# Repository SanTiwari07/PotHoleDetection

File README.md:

<div align="center">

# IPDS: Intelligent Pothole Detection System

### See it. Feel it. Map it.

**A low-cost dual-ESP32 + YOLOv8 rig that detects potholes in real time, tracks them, confirms each one with an accelerometer, and logs it with a severity score, GPS position and timestamp.**

<br>

<br><br>

**[Website](https://santiwari07.github.io/PotHoleDetection/)** ·
**[Paper](https://zenodo.org/records/20760578)** ·
**[Colab](https://colab.research.google.com/github/SanTiwari07/PotHoleDetection/blob/main/notebooks/quickstart.ipynb)** ·
**[Wokwi Simulation](https://wokwi.com/projects/453817129999607809)** ·
**[Docs](docs/)** ·
**[Contribute](CONTRIBUTING.md)**

<br>

<sub>YOLOv8m detections + SORT tracking on a sample road video. Each pothole keeps one ID and is logged once when it crosses the green reference line.</sub>

</div>

---

## Table of contents

- [Why IPDS?](#why-ipds)
- [Try it in 30 seconds](#try-it-in-30-seconds)
- [How it works](#how-it-works)
- [Results](#results)
- [Build the hardware](#build-the-hardware)
- [Repository structure](#repository-structure)
- [Contributing](#contributing)
- [Roadmap](#roadmap)
- [Citation](#citation)
- [Authors](#authors)
- [License](#license)

---

## Why IPDS?

Most pothole projects stop at "draw a box on an image". IPDS goes all the way from camera to a **geo-tagged, severity-ranked maintenance log**.

<table>
<tr>
<td width="33%" valign="top">

### Detect
YOLOv8m fine-tuned for potholes, reaching **mAP@0.5 = 81.7%**.

</td>
<td width="33%" valign="top">

### Track
SORT (Kalman filter + Hungarian matching) gives every pothole a stable ID, so each one is **counted once**, not once per frame.

</td>
<td width="33%" valign="top">

### Feel
When a tracked pothole reaches the wheel line, the hub asks a second ESP32 for an **MPU6050 accelerometer burst** and computes peak jerk.

</td>
</tr>
<tr>
<td width="33%" valign="top">

### Fuse
A pothole is logged only if the camera sees it **and** the accelerometer feels it. Severity (0–1) = 70% detection confidence + 30% measured impact.

</td>
<td width="33%" valign="top">

### Log
Every event goes to CSV with a DS3231 RTC timestamp and NEO-6M GPS fields, alongside an annotated MP4.

</td>
<td width="33%" valign="top">

### Cheap
Two ESP32 boards and common breakout modules, **under ₹2,500 per unit** (as reported in the paper). Inference runs on a laptop.

</td>
</tr>
</table>

---

## Try it in 30 seconds

No hardware? No problem. Pick whichever suits you:

| Option | What you get | Hardware needed |
|---|---|:---:|
|  | Run detection + tracking on a sample image or your own video | None |
|  | The ESP32 sensor node (MPU6050, NEO-6M GPS, DS3231) running in your browser | None |
| [`demo/app.py`](demo/) | Gradio web UI for images and videos (deployable as a Hugging Face Space) | None |
| Local install (below) | The full pipeline: offline on video, or live with ESP32 boards | Optional |

<!-- After deploying demo/ as a Hugging Face Space, add:

-->

### Local quickstart

```bash
git clone https://github.com/SanTiwari07/PotHoleDetection.git
cd PotHoleDetection
pip install -r requirements.txt

# Vision-only on any road video (weights auto-download on first run)
python python/main.py --source path/to/road_video.mp4
```

Outputs land in `outputs/videos/` (annotated MP4) and `outputs/logs/` (CSV). Press `q` to stop; add `--no-display` on servers.

---

## How it works

```mermaid
flowchart LR
    subgraph CAM["ESP32-CAM · vision node"]
        OV["OV2640 camera"]
    end

    subgraph HUB["Python processing hub"]
        direction TB
        Y["YOLOv8m detector"] --> S["SORT tracker"]
        S --> F["Geometric filters"]
        F -->|"pothole crosses line"| Q["Query sensor node"]
        Q --> G{"Impact felt?"}
        G -->|"yes"| SEV["Severity fusion"]
        G -->|"no"| X["Reject"]
        SEV --> OUT["CSV log + annotated MP4"]
    end

    subgraph SENSE["ESP32 · sensor node"]
        IMU["MPU6050 IMU"]
        GPS["NEO-6M GPS"]
        RTC["DS3231 RTC"]
    end

    OV -->|"WiFi · MJPEG"| Y
    Q -->|"GET /query?pothole_id=N"| SENSE
    SENSE -->|"JSON: accel, time, GPS"| G
```

> **Why two ESP32s?** Reading I²C sensors on the ESP32-CAM blocks `esp_camera_fb_get()` and tanks the frame rate. Moving all sensor I/O to a second, event-driven board keeps the video stream smooth, and both boards stay cheap.

| Step | Where | What happens |
|:---:|---|---|
| 1 | ESP32-CAM | Streams 320×240 MJPEG frames over WiFi |
| 2 | Hub | YOLOv8m detects → SORT assigns persistent IDs |
| 3 | Hub | Holds back tracks that are too large (> 25% of frame), too wide (aspect ratio > 3) or stationary for more than 10 frames |
| 4 | Hub | When a track's centre crosses the reference line, sends `GET /query?pothole_id=N` |
| 5 | Sensor node | Returns accelerometer, RTC timestamp and GPS fields as JSON |
| 6 | Hub | Computes peak jerk. No impact means the event is rejected; otherwise it computes severity, appends a CSV row and annotates the video |

### Severity scoring

```
jerk_norm = min(peak_jerk / 20 m/s³, 1)
severity  = 0.7 × YOLO confidence + 0.3 × jerk_norm
```

These are Eqs. 6–7 of the paper, implemented in [`python/pothole_detection/fusion.py`](python/pothole_detection/fusion.py). Events whose peak jerk is below `--jerk-threshold` (default 1.5 m/s³; calibrate it for your vehicle) are rejected by the fusion gate. In offline mode there is no sensor node, so the gate is skipped, severity is vision-only, and the jerk/GPS columns are left empty.

**Deep dives:** [Architecture](docs/ARCHITECTURE.md) · [Hardware & wiring](docs/HARDWARE.md) · [Full technical spec](docs/DETAIL.md) · [Paper (PDF)](docs/IPDS_Pothole_Detection.pdf) · [Project website](https://santiwari07.github.io/PotHoleDetection/)

---

## Results

### Model (validation split)

| mAP@0.5 | mAP@0.5:0.95 | Precision | Recall |
|:---:|:---:|:---:|:---:|
| **81.68%** | **55.95%** | **82.33%** | **74.42%** |

YOLOv8m, 640×640 input, single class (`pothole`), trained on the [Pothole Detection dataset by andrewmvd on Kaggle](https://www.kaggle.com/datasets/andrewmvd/pothole-detection) (665 images with bounding boxes; Pascal VOC XML converted to YOLO format; 598 training / 67 validation images). Weights: [Releases → v1.0](https://github.com/SanTiwari07/PotHoleDetection/releases/tag/v1.0).

```python
from ultralytics import YOLO
model = YOLO("assets/models/pothole_yolov8.pt")
model.predict("road.jpg", conf=0.25)[0].show()
```

### System performance (reported in the paper)

| Measure | Result |
|---|---|
| Inference speed | 10–15 FPS on a CPU-only laptop (320×240 input) |
| Latency, frame capture → CSV row | ~170–200 ms |
| Hardware cost | under ₹2,500 per unit |

The paper also reports false-positive trials (shadows, manhole covers, speed bumps and others); see [docs/DETAIL.md](docs/DETAIL.md#7-reported-system-results-paper).

### Sample field log (20 March 2026)

[`outputs/sample_logs/output.csv`](outputs/sample_logs/output.csv) has 50 logged potholes from a drive between 1:56 and 2:08 pm. It uses the same columns as the log `main.py` writes. The original, older-format file (text severity bands, `pothole_001` IDs, `01:56 pm` times) is kept as [`output_legacy.csv`](outputs/sample_logs/output_legacy.csv), and [`python/convert_legacy_log.py`](python/convert_legacy_log.py) converts any log in that format:

```bash
python python/convert_legacy_log.py outputs/sample_logs/output_legacy.csv -o outputs/sample_logs/output.csv
```

The script turns `01:56 pm` into `13:56:00` (the old log has no seconds, so they are `00`), `pothole_001` into `1`, and each Low / Medium / High band into the 0–1 score computed from that row's own `confidence` and `peak_jerk`. Rows already in the current format are left unchanged. The bands in the legacy file were assigned by peak jerk:

| Band | Peak jerk in the file | Rows | Share |
|---|---|:---:|:---:|
| Low | 1.6 – 2.7 | 8 | 16% |
| Medium | 3.0 – 5.9 | 22 | 44% |
| High | 6.0 – 9.4 | 20 | 40% |

<details>
<summary><b>CSV column reference</b></summary>

| Column | Description |
|---|---|
| `date`, `time` | Detection timestamp (DS3231 RTC; falls back to host clock) |
| `frame_id` | Video frame number when the event was triggered |
| `pothole_id` | Unique SORT track ID |
| `confidence` | YOLOv8 detection confidence (0–1) |
| `bounding_box_area` | Box area in px² |
| `aspect_ratio` | Box width / height |
| `peak_jerk` | Peak jerk from the MPU6050 burst (m/s³; empty in offline mode) |
| `severity` | Severity score 0–1 |
| `latitude`, `longitude` | WGS-84 position from the NEO-6M (`0` without a GPS fix; empty in offline mode) |

</details>

<details>
<summary><b>Reproduce the model</b></summary>

```bash
# 1. Download and unzip https://www.kaggle.com/datasets/andrewmvd/pothole-detection
python training/prepare_dataset.py --src path/to/pothole-detection   # VOC XML -> YOLO, 598 train / 67 val
python training/train.py                                              # YOLOv8m, 640px, 100 epochs, AdamW
```

The best checkpoint is copied to `assets/models/pothole_yolov8.pt` and validation metrics are printed at the end. The split sizes match the paper, but the paper doesn't publish which images were in each split, so your metrics may differ slightly.

</details>

---

## Build the hardware

### The prototype

Two hand-wired perfboard decks: the ESP32-CAM vision node on top, and the ESP32 sensor node with the MPU6050, DS3231 and NEO-6M below. The [custom PCB](#custom-pcb) replaces the lower deck.

<table>
<tr>
<td width="33%" align="center"><br><sub><b>Assembled rig</b>: camera deck above, sensor deck below</sub></td>
<td width="33%" align="center"><br><sub><b>Vision node</b>: ESP32-CAM with the OV2640 camera</sub></td>
<td width="33%" align="center"><br><sub><b>Hand-wired underside</b>: point-to-point wiring of the sensor deck</sub></td>
</tr>
</table>

### Components

| Component | Role |
|---|---|
| **ESP32-CAM** (AI-Thinker, OV2640) | Vision node: continuous MJPEG stream |
| **ESP32 dev board** | Sensor node: answers HTTP queries on demand |
| **MPU6050** | 6-axis IMU: peak jerk while crossing the pothole |
| **NEO-6M GPS** | Latitude / longitude |
| **DS3231 RTC** | Accurate timestamps without internet |
| **Laptop or edge device** | Runs YOLOv8 inference (e.g. Jetson Nano) |

### Sensor-node wiring

| Module pin | ESP32 pin |
|---|---|
| MPU6050 SDA / DS3231 SDA | GPIO21 (+ 4.7 kΩ pull-up to 3V3) |
| MPU6050 SCL / DS3231 SCL | GPIO22 (+ 4.7 kΩ pull-up to 3V3) |
| MPU6050 **AD0** | **3V3** (sets address 0x69; the DS3231 already uses 0x68) |
| NEO-6M TX → | GPIO16 (RX2) |
| NEO-6M RX ← | GPIO17 (TX2) |
| All VCC / GND | 3V3 / GND |

### Custom PCB

A 2-layer carrier board for the ESP32-DevKitC and the three modules is in [`KiCad/IPDS_SensorNode/`](KiCad/IPDS_SensorNode/). It passes KiCad's ERC/DRC with 0 violations, and ready-to-order Gerbers, a BOM and a schematic PDF are in its `fabrication/` folder. Interactive diagrams: [`Diagrams/`](Diagrams/).

### Setup

1. **WiFi credentials.** Both boards and the laptop join the same network (a phone hotspot works):
   ```bash
   cp .env.example .env        # then edit WIFI_SSID / WIFI_PASSWORD
   python update_wifi.py       # generates credentials.h for both sketches (git-ignored)
   ```
2. **Flash the firmware** with Arduino IDE 2.x + ESP32 core 3.x (sensor node also needs the `RTClib` and `TinyGPSPlus` libraries):

   | Sketch | Board |
   |---|---|
   | [`ESP_32_Code/esp_32_cam_final/`](ESP_32_Code/esp_32_cam_final/) | AI-Thinker ESP32-CAM |
   | [`ESP_32_Code/esp_32_final/`](ESP_32_Code/esp_32_final/) | ESP32 Dev Module |

3. **Set the device IPs** printed on each Serial Monitor (115200 baud) in `.env` (`ESP32_CAM_IP`, `ESP32_SENSOR_IP`). Open `http://<sensor-ip>/` in a browser to check that the MPU6050, RTC and GPS are all detected (the GPS needs a clear sky view for its first fix).
4. **Calibrate the MPU6050** once, mounted in the vehicle: flash [`ESP_32_Code/mpu6050_calibration`](ESP_32_Code/mpu6050_calibration/), paste the printed offsets into `esp_32_final.ino` and re-flash it ([details](docs/HARDWARE.md#mpu6050-calibration)).
5. **Run live:**
   ```bash
   python python/main.py --live
   ```

<details>
<summary><b>All CLI options</b></summary>

| Flag | Default | Description |
|---|---|---|
| `--source` | first `.mp4` in `assets/videos/` | Offline mode: video path or webcam index |
| `--live` | off | Stream from the ESP32-CAM and query the sensor node |
| `--cam-ip`, `--sensor-ip` | from `.env` | Override device IPs |
| `--model` | `assets/models/pothole_yolov8.pt` | Weights (auto-downloaded if missing) |
| `--conf` | `0.25` | Detection confidence threshold |
| `--jerk-threshold` | `1.5` | Live mode: minimum peak jerk (m/s³) that confirms an impact |
| `--output-dir` | `outputs/` | Where the MP4 and CSV are written |
| `--no-display` | off | Headless mode |

</details>

### See your potholes on a map

Convert any log to GeoJSON and open it in [geojson.io](https://geojson.io), QGIS, uMap or Google My Maps:

```bash
python python/export_geojson.py outputs/sample_logs/output.csv -o potholes.geojson
```

Rows without a GPS position (offline runs, or no GPS fix) are skipped and counted.

---

## Repository structure

```text
PotHoleDetection/
├── python/
│   ├── main.py                    # Entry point: detection → tracking → fusion → logging
│   ├── export_geojson.py          # CSV log → GeoJSON for QGIS / geojson.io
│   └── pothole_detection/
│       ├── detector.py            # YOLOv8 wrapper
│       ├── tracker.py             # SORT wrapper with unique-ID counting
│       ├── sort.py                # SORT (Bewley et al., GPL-3.0)
│       ├── filters.py             # Area / aspect-ratio / persistence filters
│       ├── fusion.py              # Jerk, fusion gate, severity score
│       └── geojson_export.py      # Log rows → GeoJSON features
├── ESP_32_Code/
│   ├── esp_32_cam_final/          # Vision node firmware (MJPEG server)
│   ├── esp_32_final/              # Sensor node firmware (HTTP /query API)
│   └── mpu6050_calibration/       # One-time MPU6050 offset calibration
├── PotHoleSimu/                   # Wokwi simulation of the sensor node
├── demo/                          # Gradio app / Hugging Face Space
├── notebooks/quickstart.ipynb     # Colab quickstart
├── training/                      # Dataset conversion + YOLOv8 training scripts
├── KiCad/                         # Sensor-node schematic and PCB
├── Diagrams/                      # Interactive HTML block diagrams
├── assets/                        # Demo GIF and hardware photos
├── index.html                     # Project website (GitHub Pages)
├── docs/                          # Architecture, hardware, full spec, paper PDF
├── outputs/sample_logs/           # Field-test CSV
├── tests/                         # Unit tests (pytest)
├── update_wifi.py                 # .env → credentials.h generator
└── .env.example                   # Config template (copy to .env)
```

---

## Contributing
PotHoleDetection is an open-source project that welcomes contributions from everyone. Whether you're fixing a bug, improving documentation, enhancing pothole detection accuracy, or adding new features, every contribution makes a difference. Real-world road images and pothole data from your city are especially valuable for improving the system.

**Good places to start**

- **Found a bug or have an idea?** [Open an issue](https://github.com/SanTiwari07/PotHoleDetection/issues/new/choose).
- **First contribution?** Look for [`good first issue`](https://github.com/SanTiwari07/PotHoleDetection/labels/good%20first%20issue) and [`help wanted`](https://github.com/SanTiwari07/PotHoleDetection/labels/help%20wanted).
- **Want something bigger?** Pick an item from the [roadmap](#roadmap) below.

**Dev setup in four commands**

```bash
git clone https://github.com/SanTiwari07/PotHoleDetection.git
cd PotHoleDetection
pip install -r requirements-dev.txt
pytest tests
```

Then fork, branch from `main`, keep each PR focused, and make sure `pytest tests` passes. **Never commit credentials** (`.env` and `credentials.h` are git-ignored). The full guide is in [**CONTRIBUTING.md**](CONTRIBUTING.md).

**Built one, or tried it on your roads?** Tell us, whatever the result. Post photos, logs or false-positive clips in [Discussions](https://github.com/SanTiwari07/PotHoleDetection/discussions) or in the [field data issue](https://github.com/SanTiwari07/PotHoleDetection/issues/10). Real-world data from other cities is the most useful contribution you can make.

### Contributors

---

## Roadmap

- [ ] Smartphone / dashcam mode (no ESP32 needed)
- [x] Export detections to GeoJSON ([`export_geojson.py`](python/export_geojson.py))
- [ ] Edge deployment on Coral TPU / Hailo-8 / Jetson
- [ ] Docker image for the processing hub
- [ ] Web dashboard with a live pothole heatmap
- [ ] Segmentation model for pothole area / depth estimation

---

## Citation

If you use IPDS in your research, please cite the paper ([Zenodo record](https://zenodo.org/records/20760578)) or the software:

```bibtex
@software{tiwari2026ipds,
  author    = {Tiwari, Sanskar and Bansod, Swarali and Kognole, Eshwari and Shinde, Shruti},
  title     = {Real-Time Pothole Detection Based on Vision-Dominant Sensor Fusion
               and Dual ESP32 Architecture},
  year      = {2026},
  version   = {1.0.0},
  license   = {MIT},
  url       = {https://github.com/SanTiwari07/PotHoleDetection}
}
```

A machine-readable [`CITATION.cff`](CITATION.cff) is included; GitHub's **"Cite this repository"** button uses it.

---

## Authors

| Name | Role |
|---|---|
| **Sanskar Tiwari** | Core architecture & ML pipeline |
| **Swarali Bansod** | Sensor integration & firmware |
| **Eshwari Kognole** | Hardware design & testing |
| **Shruti Shinde** | Data collection & validation |

## License

Project code is released under the [MIT License](LICENSE).

Third-party components keep their own licenses: [`sort.py`](python/pothole_detection/sort.py) is © Alex Bewley under **GPL-3.0**, and [Ultralytics YOLOv8](https://github.com/ultralytics/ultralytics) is **AGPL-3.0**.

---

<div align="center">

### If IPDS is useful to you, please give it a star on GitHub. It helps others find the project!

</div>

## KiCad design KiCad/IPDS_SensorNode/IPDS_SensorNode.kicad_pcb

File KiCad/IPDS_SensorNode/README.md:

# IPDS Sensor Node: KiCad PCB

Carrier board for the IPDS sensor node: an **ESP32-DevKitC (38-pin)** plus plug-in **MPU6050**, **DS3231 RTC** and **NEO-6M GPS** breakout modules. Every module sits in a female header, so nothing is soldered to the modules themselves.

**Board:** 117 × 68 mm · 2 layers · 1.6 mm FR4 · GND pour on both sides · 4 × M3 mounting holes
**Made with:** KiCad 10.0 (open with KiCad 10 or newer)

### Verification status

Checked with `kicad-cli` (KiCad 10.0.6):

| Check | Result |
|---|---|
| ERC (schematic) | **0 violations** |
| DRC (PCB, all severities) | **0 violations**, **0 unconnected items** |
| Schematic ↔ PCB parity | **0 issues** |

```bash
kicad-cli sch erc --severity-all IPDS_SensorNode.kicad_sch
kicad-cli pcb drc --severity-all --schematic-parity IPDS_SensorNode.kicad_pcb
```

---

## Files

| File | Description |
|---|---|
| `IPDS_SensorNode.kicad_pro` | Project settings and design rules |
| `IPDS_SensorNode.kicad_sch` | Schematic |
| `IPDS_SensorNode.kicad_pcb` | PCB layout |
| `IPDS.kicad_sym` | Project symbols: ESP32-DevKitC and the three breakout modules (named pins) |
| `IPDS.pretty/` | Project footprint: ESP32-DevKitC 38-pin socket |
| `fabrication/IPDS_SensorNode_gerbers.zip` | Gerbers + Excellon drill files, ready to upload to a PCB fab |
| `fabrication/IPDS_SensorNode_schematic.pdf` | Schematic as PDF |
| `fabrication/IPDS_SensorNode_BOM.csv` | Bill of materials |

---

## Connections

| Net | ESP32 pin | Connected to |
|---|---|---|
| `+3V3` | 3V3 (onboard regulator) | MPU VCC, MPU **AD0**, RTC VCC, GPS VCC, R1, R2, C1, C2 |
| `GND` | GND ×3 | All modules, J1 pin 2, C1, C2 |
| `+5V` | 5V | D1 cathode (external 5 V input) |
| `SDA` | GPIO21 | MPU SDA, RTC SDA, R1 4.7 kΩ pull-up |
| `SCL` | GPIO22 | MPU SCL, RTC SCL, R2 4.7 kΩ pull-up |
| `ESP_TX2` | GPIO17 (TX2) | GPS **RX** |
| `ESP_RX2` | GPIO16 (RX2) | GPS **TX** |
| `VIN_EXT` | n/a | J1 pin 1 → D1 anode |

### I²C addresses

| Device | Address | Note |
|---|---|---|
| DS3231 RTC | `0x68` | fixed |
| AT24C32 EEPROM (on the ZS-042 board) | `0x57` | unused |
| MPU6050 | **`0x69`** | AD0 is tied to 3V3 on this PCB, because `0x68` is already taken by the DS3231 |

The sensor firmware (`ESP_32_Code/esp_32_final`) uses exactly these pins and addresses. GPS UART runs at 9600 baud, 8N1.

### Module pin order (match the silkscreen)

| Socket | Module | Pin order (pin 1 = square pad, top) |
|---|---|---|
| U2 (1×8) | GY-521 MPU6050 | VCC, GND, SCL, SDA, XDA, XCL, AD0, INT |
| U3 (1×6) | ZS-042 DS3231 | 32K, SQW, SCL, SDA, VCC, GND |
| U4 (1×4) | GY-NEO6MV2 | VCC, RX, TX, GND |

Breakout boards from different sellers sometimes order their pins differently. **Check your module's printed labels against the table before plugging it in.**

---

## Before you order

1. **Measure your ESP32 board.** The footprint expects the two pin rows **25.4 mm (1.0") apart**, as on Espressif's DevKitC V4 and most 38-pin clones. Some "narrow" clones are 22.86 mm; if yours is, move the right-hand row in `IPDS.pretty`.
2. **Power:** feed 5 V into J1 (e.g. a car USB adapter) **or** use the DevKit's USB port. If your DevKit has no diode on its USB 5 V line, don't connect both at once: D1 stops J1 from being back-fed, but USB could be back-fed from J1.
3. **ZS-042 with a CR2032:** the module has a charging circuit meant for rechargeable LIR2032 cells. With a normal CR2032, remove its 200 Ω resistor (or the diode next to it).

## Bill of materials

| Qty | Ref | Part | Notes |
|---|---|---|---|
| 1 | U1 | ESP32-DevKitC 38-pin | plus **2 × 1×19 female headers**, 2.54 mm |
| 1 | U2 | GY-521 MPU6050 module | 1×8 female header |
| 1 | U3 | ZS-042 DS3231 module + CR2032 | 1×6 female header |
| 1 | U4 | GY-NEO6MV2 NEO-6M GPS module + antenna | 1×4 female header |
| 1 | J1 | Phoenix MKDS 1,5/2-5.08 screw terminal | or any 5.08 mm 2-pin terminal |
| 1 | D1 | SS14 Schottky diode, SMA | 1 A, 40 V |
| 2 | R1, R2 | 4.7 kΩ, 0805 | I²C pull-ups |
| 1 | C1 | 100 nF, 0805 | decoupling |
| 1 | C2 | 10 µF, 0805, ≥10 V | bulk |
| 4 | — | M3 standoffs + screws | mounting |

## Ordering the PCB

Upload `fabrication/IPDS_SensorNode_gerbers.zip` to JLCPCB, PCBWay or a similar fab with the defaults: 2 layers, 1.6 mm, HASL, 1 oz copper. All tracks are ≥ 0.25 mm and clearances ≥ 0.2 mm, so standard (cheapest) capabilities are enough.

To regenerate the outputs after editing: **File → Fabrication Outputs → Gerbers** and **Drill Files** in the PCB editor, after re-running **Inspect → Design Rules Checker**.

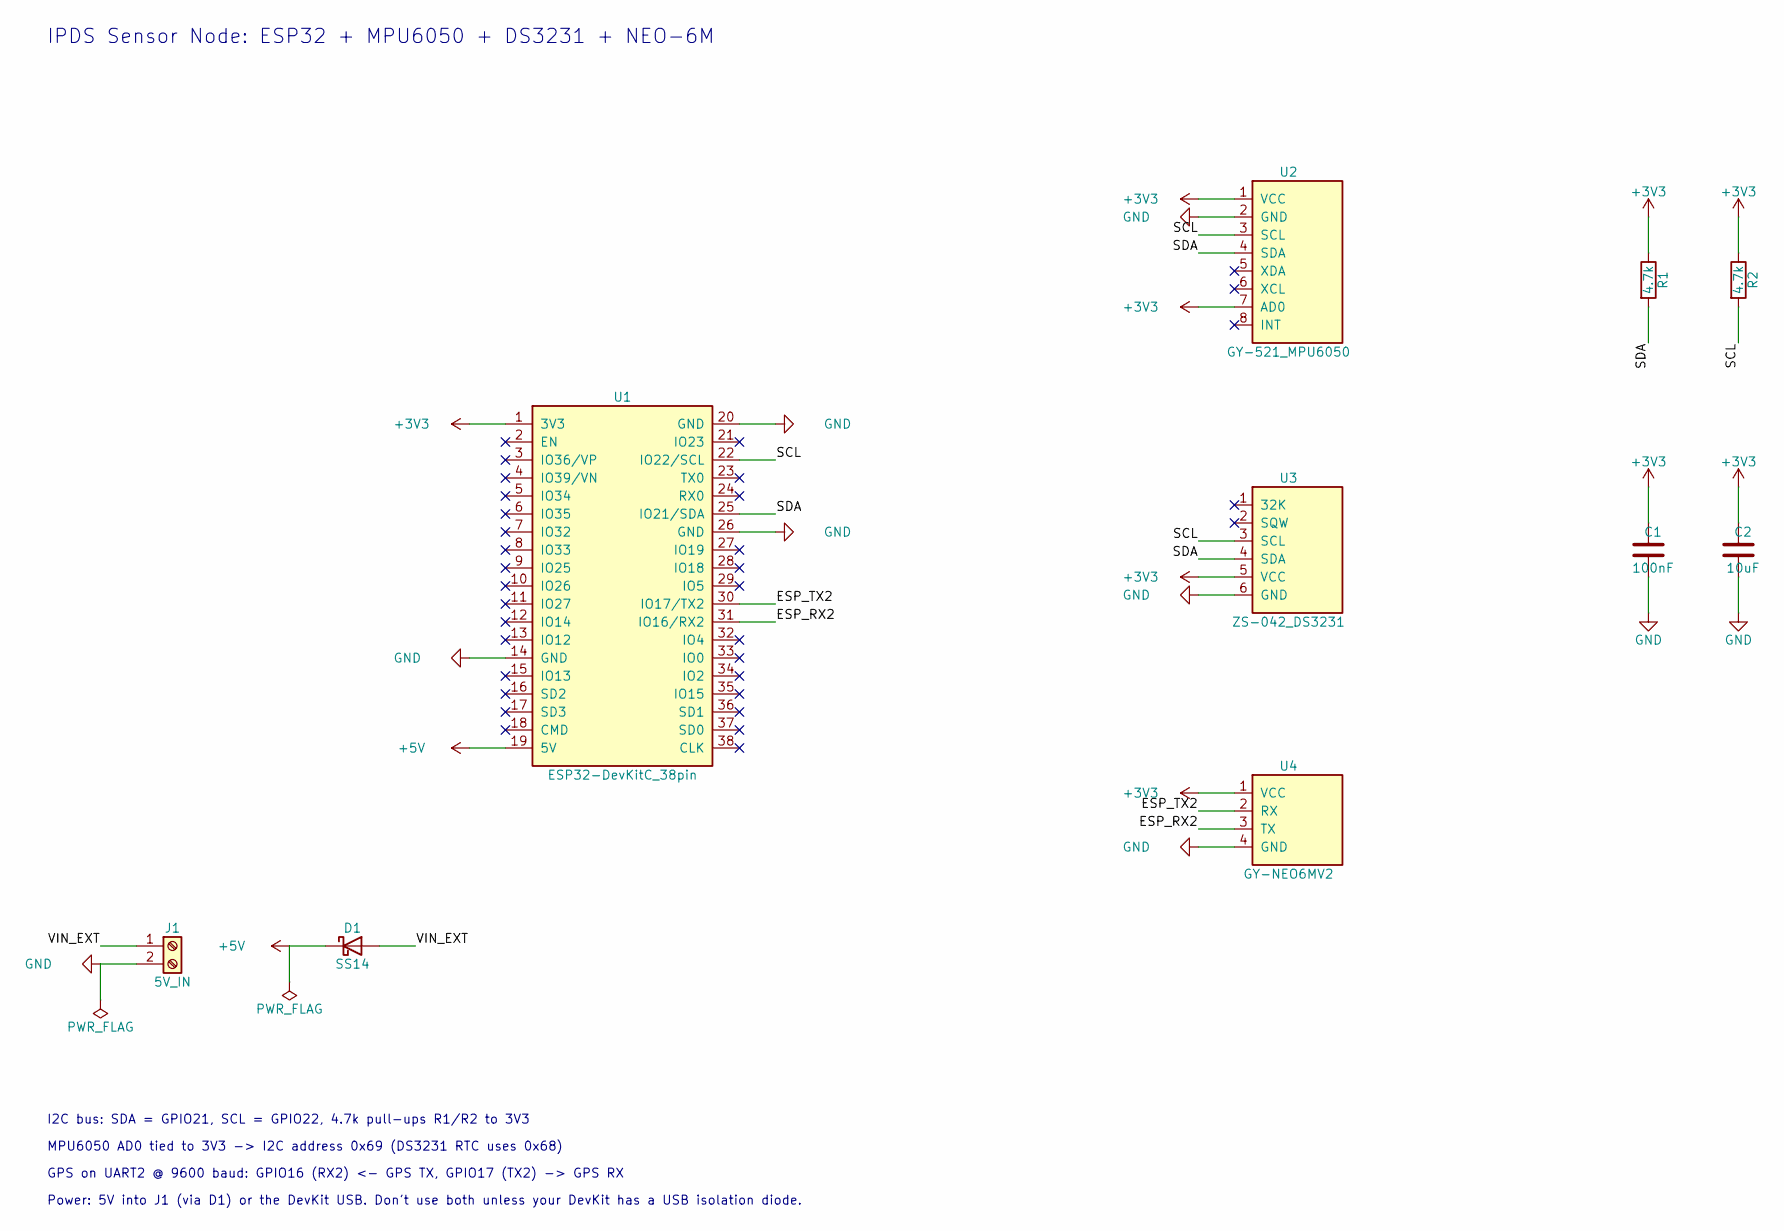
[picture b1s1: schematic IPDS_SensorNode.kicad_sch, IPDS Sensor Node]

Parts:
C1: 100nF; C_0805_2012Metric
C2: 10uF; C_0805_2012Metric
D1: SS14; D_SMA
J1: 5V_IN; TerminalBlock_Phoenix_MKDS-1,5-2-5.08_1x02_P5.08mm_Horizont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
R1, R2: 4.7k; R_0805_2012Metric
U1: ESP32-DevKitC_38pin; ESP32_DevKitC_38_Socket
U2: GY-521_MPU6050; PinSocket_1x08_P2.54mm_Vertical
U3: ZS-042_DS3231; PinSocket_1x06_P2.54mm_Vertical
U4: GY-NEO6MV2; PinSocket_1x04_P2.54mm_Vertical

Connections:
+3V3: C1.1, C2.1, R1.1, R2.1, U1.1 (3V3), U2.1 (VCC), U2.7 (AD0), U3.5 (VCC), U4.1 (VCC)
+5V: D1.1 (K), U1.19 (5V)
/ESP_RX2: U1.31 (IO16/RX2), U4.3 (TX)
/ESP_TX2: U1.30 (IO17/TX2), U4.2 (RX)
/SCL: R2.2, U1.22 (IO22/SCL), U2.3 (SCL), U3.3 (SCL)
/SDA: R1.2, U1.25 (IO21/SDA), U2.4 (SDA), U3.4 (SDA)
/VIN_EXT: D1.2 (A), J1.1
GND: C1.2, C2.2, J1.2, U1.14 (GND), U1.20 (GND), U1.26 (GND), U2.2 (GND), U3.6 (GND), U4.4 (GND)

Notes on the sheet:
IPDS Sensor Node: ESP32 + MPU6050 + DS3231 + NEO-6M
I2C bus: SDA = GPIO21, SCL = GPIO22, 4.7k pull-ups R1/R2 to 3V3
MPU6050 AD0 tied to 3V3 -> I2C address 0x69 (DS3231 RTC uses 0x68)
GPS on UART2 @ 9600 baud: GPIO16 (RX2) <- GPS TX, GPIO17 (TX2) -> GPS RX
Power: 5V into J1 (via D1) or the DevKit USB. Don't use both unless your DevKit has a USB isolation diode.

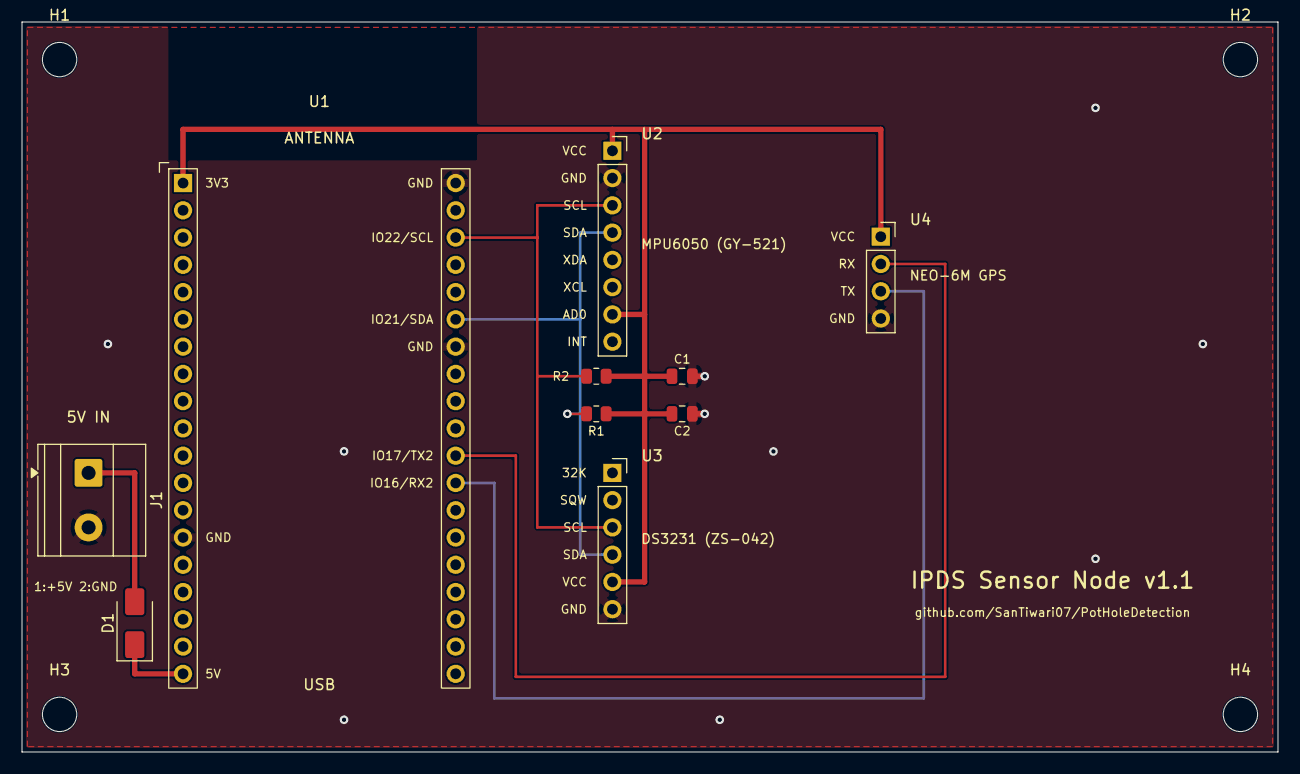
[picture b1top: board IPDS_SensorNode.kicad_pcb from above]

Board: 2 copper layers, 117.0 x 68.0 mm, 14 parts (0 on the bottom side), 8 nets.

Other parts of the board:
H1, H2, H3, H4: M3; MountingHole_3.2mm_M3

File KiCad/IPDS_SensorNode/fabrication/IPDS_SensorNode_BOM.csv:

"Refs","Value","Footprint","Qty","Description"
"C1","100nF","Capacitor_SMD:C_0805_2012Metric","1","Unpolarized capacitor"
"C2","10uF","Capacitor_SMD:C_0805_2012Metric","1","Unpolarized capacitor"
"D1","SS14","Diode_SMD:D_SMA","1","Schottky diode"
"J1","5V_IN","TerminalBlock_Phoenix:TerminalBlock_Phoenix_MKDS-1,5-2-5.08_1x02_P5.08mm_Horizontal","1","Generic screw terminal, single row, 01x02, script generated (kicad-library-utils/schlib/autogen/connector/)"
"R1,R2","4.7k","Resistor_SMD:R_0805_2012Metric","2","Resistor"
"U1","ESP32-DevKitC_38pin","IPDS:ESP32_DevKitC_38_Socket","1","ESP32-DevKitC V4 (38-pin) plugged into two 1x19 female headers, 25.4 mm row spacing"
"U2","GY-521_MPU6050","Connector_PinSocket_2.54mm:PinSocket_1x08_P2.54mm_Vertical","1","GY-521 MPU6050 accelerometer/gyro breakout, 8-pin header"
"U3","ZS-042_DS3231","Connector_PinSocket_2.54mm:PinSocket_1x06_P2.54mm_Vertical","1","ZS-042 DS3231 RTC breakout with CR2032 holder, 6-pin header"
"U4","GY-NEO6MV2","Connector_PinSocket_2.54mm:PinSocket_1x04_P2.54mm_Vertical","1","GY-NEO6MV2 u-blox NEO-6M GPS breakout, 4-pin header, 9600 baud"

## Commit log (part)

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2026-06-18 Update output.csv and fix gitignore
2026-06-18 chore: publication-ready repository restructure
    - Add comprehensive README.md (17 sections, full academic documentation)
    - Add MIT LICENSE for all 4 authors
    - Add CITATION.cff (CFF 1.2.0, all 4 authors, PICT affiliation)
    - Update .gitignore (exclude .env, __pycache__, *.pyc, .vscode/, .idea/)
    - Add outputs/sample_logs/output.csv (curated 50-detection field-test log)
    - Untrack .env and __pycache__ from version history
2026-06-18 docs: add preprint PDF and reference in README
    - Add docs/IPDS_Pothole_Detection.pdf (preprint manuscript)
    - Add Section 12 (Preprint Manuscript) to README with direct PDF link
    - Add Preprint PDF badge to README header
    - Update .gitignore to exclude *.docx source files
    - Renumber TOC sections 12–18
2026-06-22 feat: add supplementary project files and update README to reference Zenodo archiving
